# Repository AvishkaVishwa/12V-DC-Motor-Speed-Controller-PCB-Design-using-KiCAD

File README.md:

# 12V DC Motor Speed Controller PCB Design using KiCAD

This project presents a compact, low-cost, and efficient **Pulse Width Modulation (PWM)** based **DC motor speed controller** using the **NE555 timer IC** in **astable mode**, paired with a power **MOSFET** for driving a 12V DC motor. Designed in **KiCAD**, the circuit is optimized for educational, DIY, and robotics applications. This is a hardware-based controller and does not require software code for its operation.

---

## 🔧 Features

* PWM speed control for 12V DC motors
* Adjustable duty cycle using a potentiometer
* NE555 timer in astable configuration generates PWM signal
* Power MOSFET (IRFZ44N) for efficient motor drive
* Flyback protection using Schottky diode (SS14)
* 2-layer KiCAD PCB design
* Designed for high efficiency and durability

---

## 📘 Schematic Overview

### 🧹 Key Components

| Component        | Description                     | Role in Circuit Logic                     |
| ---------------- | ------------------------------- | ----------------------------------------- |
| NE555P           | Timer IC                        | Generates the PWM square wave             |
| IRFZ44N          | N-channel MOSFET                | Switches motor power ON/OFF rapidly       |
| Potentiometer R1 | Variable Resistor               | Adjusts PWM duty cycle (ON time)          |
| R2               | Fixed Resistor                  | Part of NE555 timing network              |
| D1, D2 (1N4148)  | Steering Diodes                 | Control charge/discharge paths for C2     |
| C2               | Timing Capacitor                | Sets frequency through charge cycles      |
| SS14             | Schottky Diode                  | Protects MOSFET from motor voltage spikes |
| C3               | Decoupling Capacitor (Optional) | Stabilizes NE555 power supply             |

---

## ⚙️ Circuit Operational Logic

This circuit controls motor speed by varying the **duty cycle** of a **Pulse Width Modulation (PWM)** signal generated by the NE555 timer IC operating in **astable mode** (continuous oscillation).

### 1. PWM Generation (NE555):

* The NE555 generates a square wave at Pin 3.
* Frequency and duty cycle are determined by R1 (potentiometer), R2, and C2.
* **T\_H (HIGH time)**: C2 charges through D1, R2, and upper R1.
* **T\_L (LOW time)**: C2 discharges through D2 and lower R1.
* Adjusting the potentiometer changes the ratio of T\_H to T\_L without much change in frequency.

### 2. Motor Driving (MOSFET Q1):

* NE555 output controls the Gate of IRFZ44N.
* When output is HIGH → MOSFET ON → motor powered.
* When output is LOW → MOSFET OFF → motor disconnected.
* Rapid switching provides average voltage control proportional to duty cycle.

### 3. Motor Protection (Diode D4):

* SS14 flyback diode prevents damage from back EMF when motor turns off.

---
### This is the reference design i got from Digikey..

## 🔣 Timing Equations (Astable Mode with Diodes)

Let R1 be a potentiometer (10kΩ), R2 = 1kΩ, and C2 = 0.1μF. Let `x` be the wiper position from 0 to 1.

* `R_charge = R2 + x × R1`

* `R_discharge = (1 - x) × R1`

* `T_H ≈ 0.693 × (R2 + x × R1) × C2`

* `T_L ≈ 0.693 × (1 - x) × R1 × C2`

* `T = T_H + T_L`

* `f = 1 / T`

* `Duty Cycle = (T_H / T) × 100% = ((R2 + x × R1) / (R2 + R1)) × 100%`

* ### Example:

* R1 = 10kΩ, R2 = 1kΩ, C2 = 0.1μF, x = 0.5
* T\_H = 0.693 × 6kΩ × 0.1μF ≈ 0.4158 ms
* T\_L = 0.693 × 5kΩ × 0.1μF ≈ 0.3465 ms
* Total Period ≈ 0.7623 ms → Frequency ≈ 1312 Hz
* Duty Cycle ≈ 54.5%

## The prototype Design 

---

---

<h3>📽️ Demo Video</h3>

<video src="https://github.com/user-attachments/assets/200f2159-c2bb-4788-9b7a-272e7be00f0f" controls width="600">
  Your browser does not support the video tag.
</video>

---

## 🎉 Special Thanks to PCBWay

<p align="center">
  
</p>

I would like to give a huge shoutout and sincere thanks to **[PCBWay](https://www.pcbway.com/)** for sponsoring the PCB fabrication of this project!

The **build quality, silkscreen clarity, via precision, and copper finish** exceeded expectations. PCBWay’s service was fast, professional, and extremely helpful throughout the production process.

This project wouldn’t have been possible without their generous support. If you’re looking to manufacture professional-grade PCBs at an affordable price, I highly recommend checking them out.

🔗 [Visit PCBWay →](https://www.pcbway.com/)

---

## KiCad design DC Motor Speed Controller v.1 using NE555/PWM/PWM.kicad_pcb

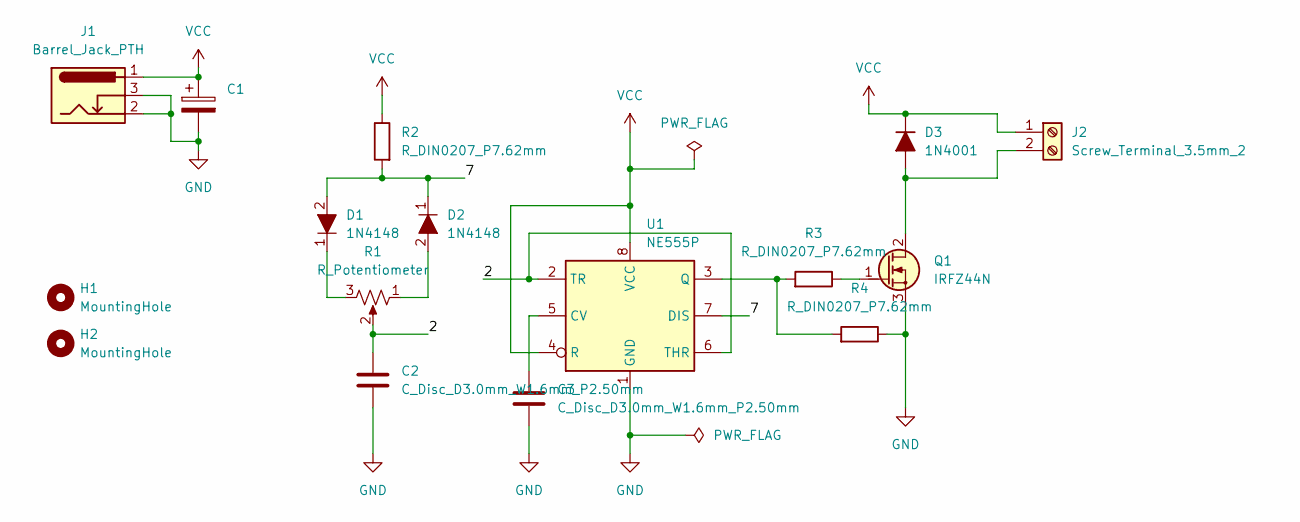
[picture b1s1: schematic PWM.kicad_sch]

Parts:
C1: CP_Radial_D5.0mm_P2.00mm
C2, C3: C_Disc_D3.0mm_W1.6mm_P2.50mm
D1, D2: 1N4148; Diode_DO-35_P10mm; MPN 1N4148; Digi-Key_PN 1N4148FS-ND
D3: 1N4001; D_DO-41_SOD81_P7.62mm_Horizontal
H1, H2: MountingHole; MountingHole_2.2mm_M2_DIN965
J1: Barrel_Jack_PTH; BarrelJack_GCT_DCJ200-10-A_Horizontal
J2: Screw_Terminal_3.5mm_2; TerminalBlock_4Ucon_1x02_P3.50mm_Horizontal
Q1: IRFZ44N; TO-220-3_Vertical_GDS
R1: R_Potentiometer; Bourns-PDB18
R2, R3, R4: R_DIN0207_P7.62mm; R_Axial_DIN0207_L6.3mm_D2.5mm_P7.62mm_Horizontal
U1: NE555P; DIP-8_W7.62mm

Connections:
/2: C2.1, R1.2, U1.2 (TR), U1.6 (THR)
/7: D1.2, D2.1, R2.1, U1.7 (DIS)
GND: C1.2, C2.2, C3.2, J1.2 (GND), J1.3 (GNDBREAK), Q1.3 (S), R4.2, U1.1 (GND)
unnamed: D1.1, R1.3
unnamed: D2.2, R1.1
unnamed: D3.2 (A), J2.2, Q1.2 (D)
unnamed: Q1.1 (G), R3.2
unnamed: C3.1, U1.5 (CV)
unnamed: R3.1, R4.1, U1.3 (Q)
VCC: C1.1, D3.1 (K), J1.1 (PWR), J2.1, R2.2, U1.4 (R), U1.8 (VCC)

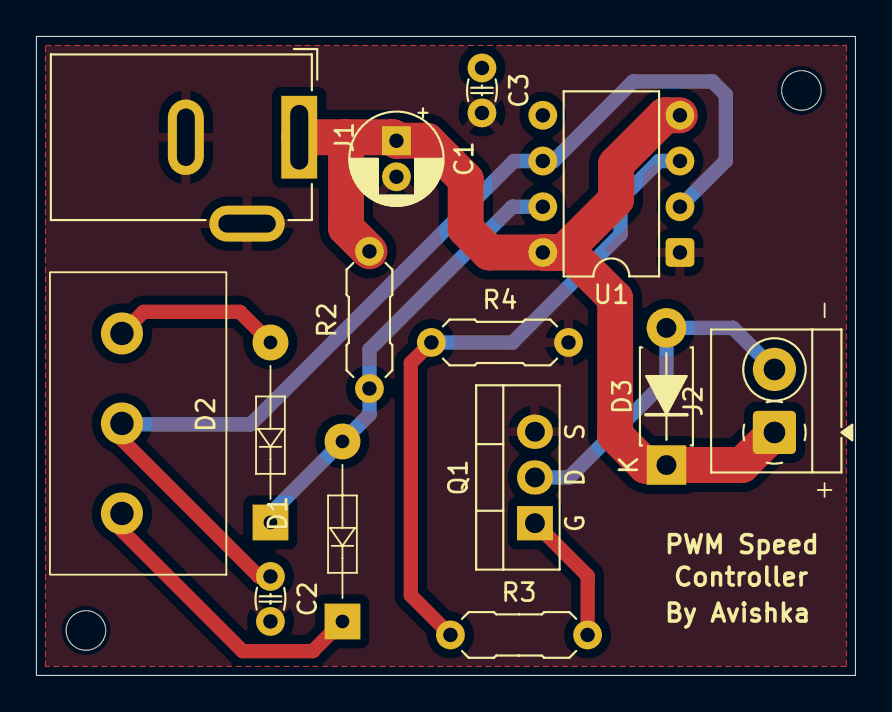
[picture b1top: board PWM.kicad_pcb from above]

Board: 2 copper layers, 45.5 x 35.5 mm, 16 parts (0 on the bottom side), 10 nets.

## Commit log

2024-09-28 PCB Design
2024-09-28 Lyaers look
2024-09-28 Schematic Design
2024-10-16 main
2025-04-18 Add files for DC Motor Speed Controller project using NE555 and PWM
2025-04-18 Update README.md to include version 1 details of the Speed Controller and related images
2025-04-18 Update PCB image for DC Motor Speed Controller project
2025-05-15 Update README.md to clarify project details and usage instructions
2025-05-15 Update schematic image in README.md to reflect version 1
2025-05-15 Update README.md to enhance schematic presentation and add new image
2025-05-15 Remove unused image files and update README.md for improved formatting
2025-05-15 Update README.md to add schematic image and improve section headers
2025-05-15 Update README.md to improve section header and replace PCB image with PWM image
2025-05-15 Update README.md to replace PWM image with DRC check image
2025-05-15 Update README.md to fix image tag formatting for PCB and DRC check images
2025-05-15 Update README.md to add PWM and PCB images for enhanced visual representation
2025-05-15 Update README.md to enhance image clarity and improve formatting
2025-05-15 Update README.md to replace schematic image tag with HTML img tag for improved rendering
2025-05-15 Update README.md to improve image formatting and enhance visual clarity
2025-05-15 Update README.md to add DRC check and PCB images for better visual representation
2025-05-15 Update README.md to add reference design and additional PCB images for enhanced clarity
2025-05-15 Update README.md to replace outdated PCB images with higher quality versions for improved clarity
2025-05-15 Update README.md to add prototype design image for better visual representation
2025-05-15 Update README.md to add demo video for enhanced user engagement
2025-05-15 Update images for PWM and PCB to improve visual quality
2025-05-15 Update PCB and PWM images in README.md for improved visual quality
2025-05-15 Update demo video link in README.md for improved accessibility
2025-05-16 Add PCB image to README.md for enhanced visual representation
2025-05-16 Remove suggestions for improvement and folder structure from README.md for clarity
2025-05-16 Remove PWM motor speed control example section from README.md for conciseness
2025-05-16 Add VSCode configuration files for C/C++ development
2025-05-16 Update PCB image for improved quality and clarity
2025-05-16 Update PCB image in README.md for better clarity
